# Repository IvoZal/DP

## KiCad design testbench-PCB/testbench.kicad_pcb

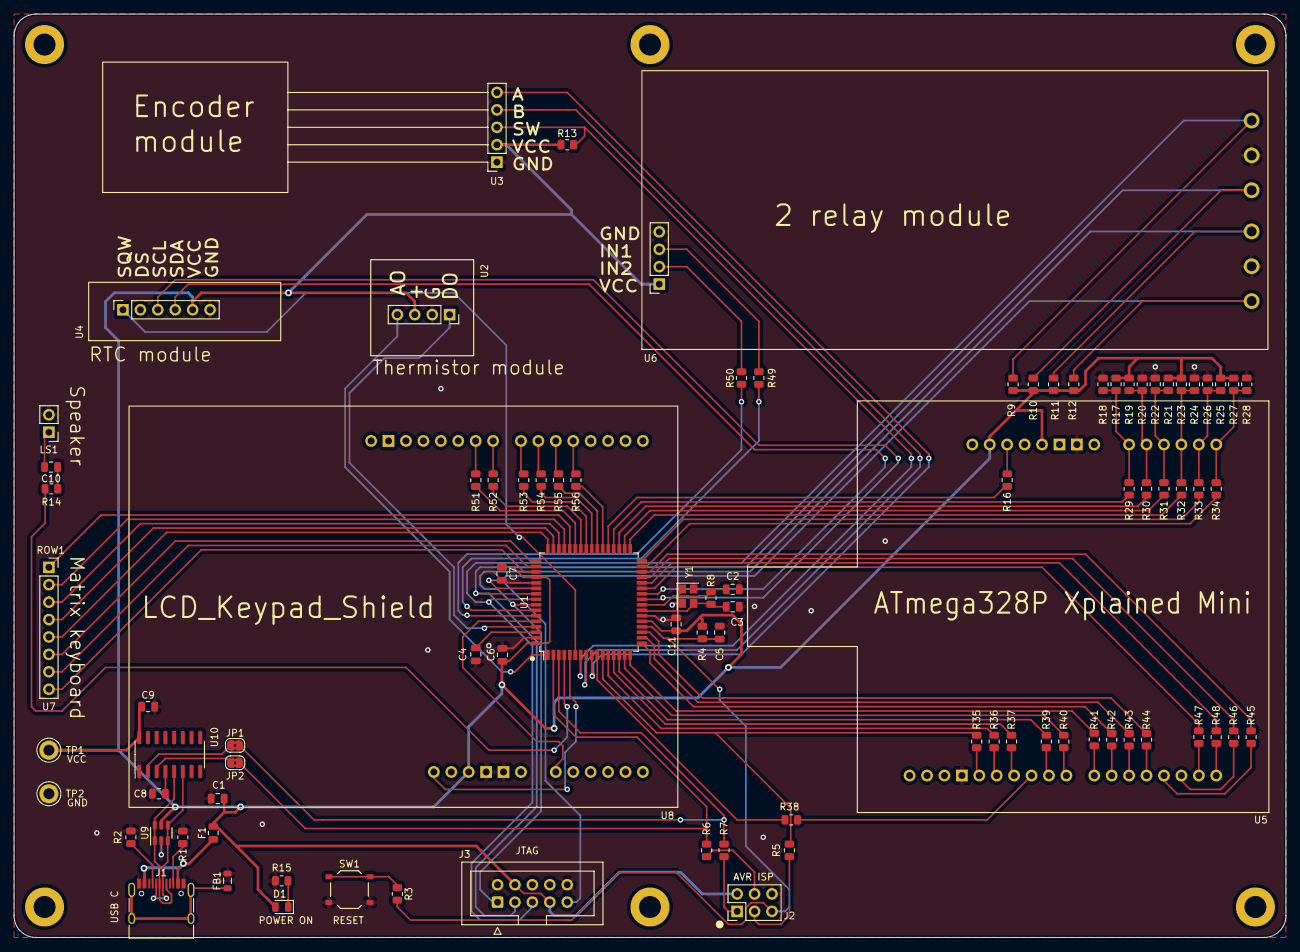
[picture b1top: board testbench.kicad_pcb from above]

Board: 2 copper layers, 185.4 x 134.6 mm, 90 parts (0 on the bottom side), 105 nets.

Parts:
C1: 4.7uF; C_0805_2012Metric
C2, C3: 22p; C_0805_2012Metric
C4, C5, C6, C7, C8, C9, C11: 100n; C_0805_2012Metric
C10: 1uF; C_0805_2012Metric
D1: LED; LED_0805_2012Metric
F1: 500mA; Fuse_0805_2012Metric
FB1: 100R@100MHz; L_0805_2012Metric
J1: USB_C_Receptacle_USB2.0; USB_C_Receptacle_HRO_TYPE-C-31-M-12
J2: AVR-ISP; PinHeader_2x03_P2.54mm_Vertical
J3: AVR-JTAG; IDC-Header_2x05_P2.54mm_Vertical
JP1, JP2: SolderJumper_2_Bridged; SolderJumper-2_P1.3mm_Bridged2Bar_RoundedPad1.0x1.5mm
LS1: Speaker; PinHeader_1x02_P2.54mm_Vertical
R1, R2: 5.1k; R_0805_2012Metric
R3, R5, R6, R7, R16, R29, R30, R31, R32, R33, R34, R35, R36, R37, R38, R39, R40, R41, R42, R43, R44, R45, R46, R47, R48, R49, R50, R51, R52, R53, R54, R55, R56: 330R; R_0805_2012Metric
R4: 4.7k; R_0805_2012Metric
R8: 1M; R_0805_2012Metric
R9, R10, R11, R12, R13: 10k; R_0805_2012Metric
R14: 200R; R_0805_2012Metric
R15: 470R; R_0805_2012Metric
R17, R18, R19, R20, R21, R22, R23, R24, R25, R26, R27, R28: 1k; R_0805_2012Metric
SW1: SW_Push; SW_Push_1P1T_XKB_TS-1187A
TP1, TP2: TestPoint; TestPoint_Keystone_5005-5009_Compact
U1: ATmega2561-16A; TQFP-64_14x14mm_P0.8mm
U2: Thermistor_module
U3: Rotary_encoder_switch_module; Rotary_encoder_module
U4: RTC_EEPROM_module; RTC_module
U5: ATmega328P_Xplained_mini
U6: Relay_module
U7: Matrix_keyboard; PinSocket_1x08_P2.54mm_Vertical
U8: LCD_display; LCD_1602A_module
U9: USBLC6-2SC6; SOT-23-6
U10: CH340C; SOIC-16_3.9x9.9mm_P1.27mm
Y1: X322516MLB4SI; Oscillator_SMD_Abracon_ASE-4Pin_3.2x2.5mm

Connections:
+5V: C1.1, C6.1, C7.1, C9.1, C11.1, D1.2 (A), F1.2, J2.2 (VCC), J3.4 (VREF), J3.7 (VCC), R4.1, R9.1, R10.1, R11.1, R12.1, R13.1, R17.1, R19.1, R21.1, R23.1, R25.1, R27.1, TP1.1, U1.21 (VCC), U1.52 (VCC), U1.64 (AVCC), U2.3 (+), U3.4 (+), U4.5 (VCC), U5.20 (VCC), U5.23 (5V), U6.4 (Vcc), U8.19 (5V), U9.5 (VBUS), U10.16 (VCC)
/ATmega328P module/D0: R16.2, U5.21 (~RESET/PC6)
/ATmega328P module/D1: R17.2, R18.1, R29.2, U5.27 (PC0)
/ATmega328P module/D2: R19.2, R20.1, R30.2, U5.28 (PC1)
/ATmega328P module/D3: R21.2, R22.1, R31.2, U5.29 (PC2)
/ATmega328P module/D4: R23.2, R24.1, R32.2, U5.30 (PC3)
/ATmega328P module/D5: R25.2, R26.1, R33.2, U5.31 (PC4)
/ATmega328P module/D6: R27.2, R28.1, R34.2, U5.32 (PC5)
/ATmega328P module/D7: R35.1, U5.14 (PB5)
/ATmega328P module/D8: R36.1, U5.13 (PB4)
/ATmega328P module/D9: R37.1, U5.12 (PB3)
/ATmega328P module/D10: R38.1, U5.11 (PB2)
/ATmega328P module/D11: R39.1, U5.10 (PB1)
/ATmega328P module/D12: R40.1, U5.9 (PB0)
/ATmega328P module/D13: R41.1, U5.8 (PD7)
/ATmega328P module/D14: R42.1, U5.7 (PD6)
/ATmega328P module/D15: R43.1, U5.6 (PD5)
/ATmega328P module/D16: R44.1, U5.5 (PD4)
/ATmega328P module/D17: R45.1, U5.4 (PD3)
/ATmega328P module/D18: R46.1, U5.3 (PD2)
/ATmega328P module/D19: R47.1, U5.2 (PD1)
/ATmega328P module/D20: R48.1, U5.1 (PD0)
/ATmega328P module/DUT_D0: R16.1, U1.37 (PC2)
/ATmega328P module/DUT_D1: R29.1, U1.36 (PC1)
/ATmega328P module/DUT_D2: R30.1, U1.35 (PC0)
/ATmega328P module/DUT_D3: R31.1, U1.34 (PG1)
/ATmega328P module/DUT_D4: R32.1, U1.33 (PG0)
/ATmega328P module/DUT_D5: R33.1, U1.32 (PD7)
/ATmega328P module/DUT_D6: R34.1, U1.31 (PD6)
/ATmega328P module/DUT_D7: R48.2, U1.28 (PD3)
/ATmega328P module/DUT_D8: R47.2, U1.27 (PD2)
/ATmega328P module/DUT_D9: R46.2, U1.29 (PD4)
/ATmega328P module/DUT_D10: R45.2, U1.30 (PD5)
/ATmega328P module/DUT_D11: R44.2, U1.19 (PG4)
/ATmega328P module/DUT_D12: R43.2, U1.18 (PG3)
/ATmega328P module/DUT_D13: R42.2, U1.17 (PB7)
/ATmega328P module/DUT_D14: R41.2, U1.16 (PB6)
/ATmega328P module/DUT_D15: R40.2, U1.15 (PB5)
/ATmega328P module/DUT_D16: R39.2, U1.14 (PB4)
/ATmega328P module/DUT_D17: R38.2, U1.10 (PB0)
/ATmega328P module/DUT_D18: R37.2, U1.13 (PB3)
/ATmega328P module/DUT_D19: R36.2, U1.12 (PB2)
/ATmega328P module/DUT_D20: R5.1, R35.2, U1.11 (PB1)
/Kit modules/ENC.A: U1.9 (PE7), U3.1 (CLK)
/Kit modules/ENC.B: U1.8 (PE6), U3.2 (DT)
/Kit modules/ENC.SW: R13.2, U1.7 (PE5), U3.3 (SW)
/Kit modules/I2C_SCL: U1.25 (PD0), U4.3 (SCL)
/Kit modules/I2C_SDA: U1.26 (PD1), U4.4 (SDA)
/Kit modules/K1-IN: R49.1, U1.58 (PF3)
/Kit modules/K1-NC: J3.5 (TMS), R9.2, U1.56 (PF5), U6.5 (K1-NC)
/Kit modules/K1-NO: J3.3 (TDO), R10.2, U1.55 (PF6), U6.7 (K1-NO)
/Kit modules/K2-IN: R50.1, U1.59 (PF2)
/Kit modules/K2-NC: J3.1 (TCK), R11.2, U1.57 (PF4), U6.8 (K2-NC)
/Kit modules/K2-NO: J3.9 (TDI), R12.2, U1.54 (PF7), U6.10 (K2-NO)
/Kit modules/KEY_D0: U1.44 (PA7), U7.1 (ROW1)
/Kit modules/KEY_D1: U1.45 (PA6), U7.2 (ROW2)
/Kit modules/KEY_D2: U1.46 (PA5), U7.3 (ROW3)
/Kit modules/KEY_D3: U1.47 (PA4), U7.4 (ROW4)
/Kit modules/KEY_D4: U1.48 (PA3), U7.5 (COL1)
/Kit modules/KEY_D5: U1.49 (PA2), U7.6 (COL2)
/Kit modules/KEY_D6: U1.50 (PA1), U7.7 (COL3)
/Kit modules/KEY_D7: U1.51 (PA0), U7.8 (COL4)
/Kit modules/LCD_AO: U1.60 (PF1), U8.23 (A0)
/Kit modules/LCD_D0: R56.2, U1.38 (PC3)
/Kit modules/LCD_D1: R55.2, U1.39 (PC4)
/Kit modules/LCD_D2: R54.2, U1.40 (PC5)
/Kit modules/LCD_D3: R53.2, U1.41 (PC6)
/Kit modules/LCD_D4: R52.2, U1.42 (PC7)
/Kit modules/LCD_D5: R51.2, U1.43 (PG2)
/Kit modules/LCD_D6: U1.5 (PE3), U8.17 (RST)
/Kit modules/RTC_SQW: U1.6 (PE4), U4.1 (SQ)
/Kit modules/Speaker_IN: R14.1, U1.4 (PE2)
/Kit modules/Thermistor_AO: U1.61 (PF0), U2.1 (AO)
/Kit modules/Thermistor_DO: U1.1 (PG5), U2.4 (DO)
/MCU/RST: C5.1, J2.5 (~RST), R3.2, R4.2, U1.20 (~RESET)
/MCU/UART0_RXD: JP2.2 (B), R6.1, U1.2 (PE0)
/MCU/UART0_TXD: JP1.2 (B), R7.1, U1.3 (PE1)
/USB Interface/VBUS: F1.1, J1.A4 (VBUS), J1.A9 (VBUS), J1.B4 (VBUS), J1.B9 (VBUS)
GND: C1.2, C2.1, C3.1, C4.2, C5.2, C6.2, C7.2, C8.2, C9.2, C11.2, FB1.2, J1.A1 (GND), J1.A12 (GND), J1.B1 (GND), J1.B12 (GND), J2.6 (GND), J3.2 (GND), J3.10 (GND), LS1.2, R1.2, R2.2, R15.2, R18.2, R20.2, R22.2, R24.2, R26.2, R28.2, SW1.2, TP2.1, U1.22 (GND), U1.53 (GND), U1.63 (GND), U2.2 (GND), U3.5 (GND), U4.6 (GND), U5.15 (GND), U5.25 (GND), U6.1 (GND), U6.6 (K1-COM), U6.9 (K2-COM), U8.20 (GND), U8.21 (GND), U9.2 (GND), U10.1 (GND), Y1.2, Y1.4
unnamed: C10.1, R14.2
unnamed: C10.2, LS1.1
unnamed: D1.1 (K), R15.1
unnamed: J1.A5 (CC1), R2.1
unnamed: J1.B5 (CC2), R1.1
unnamed: FB1.1, J1.S1 (SHIELD)
unnamed: J2.1 (MISO), R7.2
unnamed: J2.4 (MOSI), R6.2
unnamed: J2.3 (SCK), R5.2
unnamed: JP1.1 (A), U10.2 (TXD)
unnamed: JP2.1 (A), U10.3 (RXD)
unnamed: R3.1, SW1.1
unnamed: C4.1, U1.62 (AREF)
unnamed: C2.2, R8.1, U1.24 (XTAL1), Y1.1
unnamed: C3.2, R8.2, U1.23 (XTAL2), Y1.3
unnamed: R49.2, U6.2 (IN1)
unnamed: R50.2, U6.3 (IN2)
unnamed: R56.1, U8.5 (D4)
unnamed: R55.1, U8.6 (D5)
unnamed: R54.1, U8.7 (D6)
unnamed: R53.1, U8.8 (D7)
unnamed: R51.1, U8.10 (E)
unnamed: R52.1, U8.9 (RS)
unnamed: J1.A6 (D+), J1.B6 (D+), U9.1 (I/O1), U9.6 (I/O1), U10.5 (UD+)
unnamed: J1.A7 (D-), J1.B7 (D-), U9.3 (I/O2), U9.4 (I/O2), U10.6 (UD-)
unnamed: C8.1, U10.4 (V3)

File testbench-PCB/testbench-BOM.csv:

"Id";"Designator";"Footprint";"Quantity";"Designation";"Supplier and ref";
1;"U8";"LCD_1602A_module";1;"LCD_display";;;
2;"C4,C7,C9,C11,C8,C6,C5";"C_0805_2012Metric";7;"100n";;;
3;"U6";"Relay_module";1;"Relay_module";;;
4;"C10";"C_0805_2012Metric";1;"1uF";;;
5;"R23,R17,R21,R28,R20,R27,R22,R24,R18,R25,R19,R26";"R_0805_2012Metric";12;"1k";;;
6;"C3,C2";"C_0805_2012Metric";2;"22p";;;
7;"R2,R1";"R_0805_2012Metric";2;"5.1k";;;
8;"R10,R12,R11,R13,R9";"R_0805_2012Metric";5;"10k";;;
9;"R7,R5,R6,R3";"R_0805_2012Metric";4;"330R";;;
10;"D1";"LED_0805_2012Metric";1;"LED";;;
11;"J1";"USB_C_Receptacle_HRO_TYPE-C-31-M-12";1;"USB_C_Receptacle_USB2.0";;;
12;"U9";"SOT-23-6";1;"USBLC6-2SC6";;;
13;"U1";"TQFP-64_14x14mm_P0.8mm";1;"ATmega2561-16A";;;
14;"J2";"PinHeader_2x03_P2.54mm_Vertical";1;"AVR-ISP";;;
15;"R14";"R_0805_2012Metric";1;"200R";;;
16;"TP2 GND,TP1 +5V";"TestPoint_Keystone_5005-5009_Compact";2;"TestPoint";;;
17;"R8";"R_0805_2012Metric";1;"1M";;;
18;"U4";"RTC_module";1;"RTC_EEPROM_module";;;
19;"U7";"PinSocket_1x08_P2.54mm_Vertical";1;"Matrix_keyboard";;;
20;"C1";"C_0805_2012Metric";1;"10u";;;
21;"U2";"Thermistor_module";1;"Thermistor_module";;;
22;"U10";"SOIC-16_3.9x9.9mm_P1.27mm";1;"CH340C";;;
23;"JP2,JP1";"SolderJumper-2_P1.3mm_Bridged2Bar_RoundedPad1.0x1.5mm";2;"SolderJumper_2_Bridged";;;
24;"FB1";"L_0805_2012Metric";1;"100R@100MHz";;;
25;"R4";"R_0805_2012Metric";1;"4.7k";;;
26;"Y1";"Oscillator_SMD_Abracon_ASE-4Pin_3.2x2.5mm";1;"X322516MLB4SI";;;
27;"R15";"R_0805_2012Metric";1;"500R";;;
28;"LS1";"PinHeader_1x02_P2.54mm_Vertical";1;"Speaker";;;
29;"J3";"IDC-Header_2x05_P2.54mm_Vertical";1;"AVR-JTAG";;;
30;"U3";"Rotary_encoder_module";1;"Rotary_encoder_switch_module";;;
31;"SW1";"SW_Push_1P1T_XKB_TS-1187A";1;"SW_Push";;;
32;"F1";"Fuse_1812_4532Metric";1;"Polyfuse";;;
33;"U5";"ATmega328P_Xplained_mini";1;"~";;;

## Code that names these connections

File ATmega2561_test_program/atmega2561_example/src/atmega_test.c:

/*
 * atmega_test.c
 *
 * Created: 01.03.2024 11:15:49
 *  Author: Ivo Zaludek
 */ 

#include "module_test.h"

/* Pin define on ATmega2561 side */
//#define D0 (1 << PC2)		// m328p RESET
#define D1 (1 << PC1)
#define D2 (1 << PC0)
#define D3 (1 << PG1)
#define D4 (1 << PG0)
#define D5 (1 << PD7)
#define D6 (1 << PD6)
//#define D7 (1 << PD3)		// m328p USART rx
//#define D8 (1 << PD2)		// m328p USART tx
#define D9 (1 << PD4)
#define D10 (1 << PD5)
#define D11 (1 << PG4)
#define D12 (1 << PG3)
#define D13 (1 << PB7)
#define D14 (1 << PB6)
#define D15 (1 << PB5)
#define D16 (1 << PB4)
#define D17 (1 << PB0)
#define D18 (1 << PB3)
#define D19 (1 << PB2)
#define D20 (1 << PB1)

#define RST PC2				// m328p RESET

#define PB_PINS (D13 | D14 | D15 | D16 | D17 | D18 | D19 | D20)
#define PC_PINS (D1 | D2)
#define PD_PINS (D5 | D6 | D9 | D10)
#define PG_PINS (D3 | D4 | D11 | D12)

/************************************************
Local variables
*************************************************/
bool test_failed = false;

typedef struct pin_connection {
	const uint8_t m2561_port_offset;
	uint8_t m2561_pin;
	const char* m328p_pin_name;	
} PIN_CONNECTION_T;

PIN_CONNECTION_T pin_def[] =
	{{0x06,D1,"PC0"},
	{0x06,D2,"PC1"},
	{0x12,D3,"PC2"},
	{0x12,D4,"PC3"},
	{0x12,D5,"PC4"},
	{0x09,D6,"PC5"},
	//{0x09,D7,"PD0"},
	//{0x09,D8,"PD1"},
	{0x09,D9,"PD2"},
	{0x09,D10,"PD3"},
	{0x12,D11,"PD4"},
	{0x12,D12,"PD5"},
	{0x03,D13,"PD6"},
	{0x03,D14,"PD7"},
	{0x03,D15,"PB0"},
	{0x03,D16,"PB1"},
	{0x03,D17,"PB2"},
	{0x03,D18,"PB3"},
	{0x03,D19,"PB4"},
	{0x03,D20,"PB5"}};
		
/************************************************
Function declaration
*************************************************/
static void dio_input_test(bool tested_value, bool* comm_fail)
{
	char input_string[BUFFER_SIZE];
	
	PORTB_set_port_level(PB_PINS, tested_value);
	PORTC_set_port_level(PC_PINS, tested_value);
	PORTD_set_port_level(PD_PINS, tested_value);
	PORTG_set_port_level(PG_PINS, tested_value);
	
	char tested_char;
	if(tested_value == true)
		tested_char = 0x30;	// "0"
	else
		tested_char = 0x31; // "1"
		
	fprintf(&UART_1_stream,"dio_high_PD3\n");
	
	for(uint8_t i=0; i < sizeof(pin_def)/sizeof(PIN_CONNECTION_T); i++)
	{
		fprintf(&UART_1_stream,"dio_read_%s\n",pin_def[i].m328p_pin_name);
		uint32_t timestamp = getTime() + 50000;	// set response timeout
		while(timestamp > getTime())
		{
			if((UART1_buf_peek_head() == 0xA) && (UART1_buf_length() > 0))	// if the last char was line feed
			{
				for(uint8_t j=0; j < BUFFER_SIZE; j++)
				{
					if(UART1_buf_length() > 0)
						input_string[j] = UART1_buf_get();
					else
						input_string[j] = 0;
				}
				if(input_string[4] == tested_char)
				{
					printf("FAIL: %s\n",pin_def[i].m328p_pin_name);
					test_failed = true;
				}
				else if(input_string[4] == 0)
					*comm_fail = true;
				timestamp = 0;
			}
		}
		if(timestamp > 0)
			*comm_fail = true;
	}
}

static void dio_output_test(void)
{
	for(uint8_t i=0; i < sizeof(pin_def)/sizeof(PIN_CONNECTION_T); i++)
	{
		fprintf(&UART_1_stream,"dio_high_%s\n",pin_def[i].m328p_pin_name);
	}
	delay(50000);
	if((PORTB_get_port_level(0) & PB_PINS) != PB_PINS) {
		printf("FAIL: PORTB ");
		test_failed = true;
	}
	if((PORTC_get_port_level(0) & PC_PINS) != PC_PINS) {
		printf("FAIL: PORTC ");
		test_failed = true;
	}
	if((PORTD_get_port_level(0) & PD_PINS) != PD_PINS) {
		printf("FAIL: PORTD ");
		test_failed = true;
	}
	if((PORTG_get_port_level(0) & PG_PINS) != PG_PINS) {
		printf("FAIL: PORTG ");
		test_failed = true;
	}
		
	for(uint8_t i=0; i < sizeof(pin_def)/sizeof(PIN_CONNECTION_T); i++)
	{
		fprintf(&UART_1_stream,"dio_low_%s\n",pin_def[i].m328p_pin_name);
	}
	delay(50000);
	if((PORTB_get_port_level(0) & PB_PINS) != 0) {
		printf("FAIL: PORTB ");
		test_failed = true;
	}
	if((PORTC_get_port_level(0) & PC_PINS) != 0) {
		printf("FAIL: PORTC ");
		test_failed = true;
	}
	if((PORTD_get_port_level(0) & PD_PINS) != 0) {
		printf("FAIL: PORTD ");
		test_failed = true;
	}
	if((PORTG_get_port_level(0) & PG_PINS) != 0) {
		printf("FAIL: PORTG ");
		test_failed = true;
	}
}

static uint16_t adc_receive(bool* comm_fail)
{
	uint32_t timestamp = getTime() + 50000;	// set response timeout
	while(timestamp > getTime())
	{
		if((UART1_buf_peek_head() == 0xA) && (UART1_buf_length() > 0))	// if the last char was line feed
		{
			uint16_t adc_val = 0;
			char buf_ch = 0;
			while((buf_ch != 0x3D) && (UART1_buf_length() > 0))
			{
				buf_ch = UART1_buf_get();
			}
			while((buf_ch != 0xA) && (UART1_buf_length() > 0))
			{
				uint8_t buf_ch = UART1_buf_get();
				if(buf_ch > 0x29 && buf_ch < 0x3A)
				{
					adc_val = adc_val * 10U;
					adc_val += buf_ch - 0x30;
				}
				else if(buf_ch != 0xA)
					*comm_fail = true;
			}
			timestamp = 0;
			return adc_val;
		}
	}
	if(timestamp > 0)
		*comm_fail = true;
	return 0xFFFF;
}

static void adc_test(bool* comm_fail)
{	
	/* Set atmega2561 pins to Hi-Z */
	PORTB_set_port_dir(PB_PINS, PORT_DIR_IN);
	PORTC_set_port_dir(PC_PINS, PORT_DIR_IN);
	PORTD_set_port_dir(PD_PINS, PORT_DIR_IN);
	PORTG_set_port_dir(PG_PINS, PORT_DIR_IN);
	
	uint16_t adc_val;
	fprintf(&UART_1_stream,"aio_read_ADCF\n");
	adc_val = adc_receive(comm_fail);
	if(adc_val > 20) {
		printf("FAIL: ADC 0V REF");
		test_failed = true;
	}
	
	fprintf(&UART_1_stream,"aio_read_ADCE\n");
	adc_receive(comm_fail);
	delay(1000);	// wait for the reference voltage to stabilize
	// read stabilized voltage reference
	fprintf(&UART_1_stream,"aio_read_ADCE\n");
	adc_val = adc_receive(comm_fail);
	if(adc_val < 160 || adc_val > 270)
	{
		printf("FAIL: ADC VBG REF: %u",adc_val);
		test_failed = true;
	}
	
	/* For ADC channel 0 to 5 */
	for(uint8_t adc_ch=0; adc_ch <= 0x5; adc_ch++)
	{
		fprintf(&UART_1_stream,"aio_read_ADC%u\n",adc_ch);
		adc_val = adc_receive(comm_fail);
		if(adc_val < 410 || adc_val > 613)
		{
			printf("FAIL: ADC%u",adc_ch);
			test_failed = true;
		}
	}
	
	/* Set atmega2561 pins as output */
	PORTB_set_port_dir(PB_PINS, PORT_DIR_OUT);
	PORTC_set_port_dir(PC_PINS, PORT_DIR_OUT);
	PORTD_set_port_dir(PD_PINS, PORT_DIR_OUT);
	PORTG_set_port_dir(PG_PINS, PORT_DIR_OUT);
	
	PORTB_set_port_level(PB_PINS, false);
	PORTC_set_port_level(PC_PINS, false);
	PORTD_set_port_level(PD_PINS, false);
	PORTG_set_port_level(PG_PINS, false);
	
	/* For ADC channel 0 to 5 */
	for(uint8_t adc_ch=0; adc_ch <= 0x5; adc_ch++)
	{
		fprintf(&UART_1_stream,"aio_read_ADC%u\n",adc_ch);
		adc_val = adc_receive(comm_fail);
		if(adc_val < 170 || adc_val > 255)
		{
			printf("FAIL: ADC%u",adc_ch);
			test_failed = true;
		}
	}
	
	PORTB_set_port_level(PB_PINS, true);
	PORTC_set_port_level(PC_PINS, true);
	PORTD_set_port_level(PD_PINS, true);
	PORTG_set_port_level(PG_PINS, true);
	
	/* For ADC channel 0 to 5 */
	for(uint8_t adc_ch=0; adc_ch <= 0x5; adc_ch++)
	{
		fprintf(&UART_1_stream,"aio_read_ADC%u\n",adc_ch);
		adc_val = adc_receive(comm_fail);
		if(adc_val < 607 || adc_val > 911)
		{
			printf("FAIL: ADC%u",adc_ch);
			test_failed = true;
		}
	}
}

void atmega_test(void)
{
	/* Set atmega2561 pins as output */
	PORTB_set_port_dir(PB_PINS, PORT_DIR_OUT);
	PORTC_set_port_dir(PC_PINS, PORT_DIR_OUT);
	PORTD_set_port_dir(PD_PINS, PORT_DIR_OUT);
	PORTG_set_port_dir(PG_PINS, PORT_DIR_OUT);
	
	bool comm_fail = false;
	test_failed = false;
	
	/* Read both logical values */
	dio_input_test(true, &comm_fail);
	if(!comm_fail)
	{
		dio_input_test(false, &comm_fail);
	}
	
	/* Set atmega2561 pins as input */
	PORTB_set_port_dir(PB_PINS, PORT_DIR_IN);
	PORTC_set_port_dir(PC_PINS, PORT_DIR_IN);
	PORTD_set_port_dir(PD_PINS, PORT_DIR_IN);
	PORTG_set_port_dir(PG_PINS, PORT_DIR_IN);
	
	/* Set both logical values */
	if(!comm_fail)
	{
		dio_output_test();
		adc_test(&comm_fail);
	}
	
	if(comm_fail)
	{
		printf("FAIL: COMMUNICATION\n");
		test_failed = true;
	}
	if(test_failed == false)
	{
		printf("PASS");
	}
	printf("\n");
}

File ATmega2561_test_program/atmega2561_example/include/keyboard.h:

/*
 * keyboard.h - library for matrix keyboard
 *
 * Created: 16.03.2023 20:31:06
 *  Author: Ivo Zaludek
 *
 * This header file contains function and variable declarations for
 * the lcd.h library. These declarations are needed by any code
 * that uses the library, so this file should be included in all source
 * files that use the library.
 *
 * Note: This file should be included after any system or third-party
 * header files that are needed by the library. 
 */ 


#ifndef KEYBOARD_H_
#define KEYBOARD_H_

#include <avr/io.h>

/* Pinout definitions */
#define Row1 (1 << PA0)
#define Row2 (1 << PA1)
#define Row3 (1 << PA2)
#define Row4 (1 << PA3)
#define Col1 (1 << PA4)
#define Col2 (1 << PA5)
#define Col3 (1 << PA6)
#define Col4 (1 << PA7)

#define ALL_ROWS (Row1 | Row2 | Row3 | Row4)
#define ALL_COL (Col1 | Col2 | Col3 | Col4)

#define BTN_NUM 16

/* Function returns index of pressed button on the matrix keyboard */
uint8_t KeyboardReadIdx();

/* Function returns pressed button on the matrix keyboard as a char. */
char KeyboardRead();

#endif /* KEYBOARD_H_ */

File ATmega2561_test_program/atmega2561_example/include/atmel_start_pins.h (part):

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#include <port.h>

/**
 * \brief Set PB1 pull mode
 *
 * Configure pin to pull up, down or disable pull mode, supported pull
 * modes are defined by device used
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}

/**
 * \brief Set PB1 data direction
 *
 * Select if the pin data direction is input, output or disabled.
 * If disabled state is not possible, this function throws an assert.
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}

/**
 * \brief Set PB1 level
 *
 * Sets output level on a pin
 *
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}

/**
 * \brief Toggle output level on PB1
 *
 * Toggle the pin level
 */
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}

/**
 * \brief Get level on PB1
 *
 * Reads the level on a pin
 */
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}

/**
 * \brief Set PB2 pull mode
 *
 * Configure pin to pull up, down or disable pull mode, supported pull
 * modes are defined by device used
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}

/**
 * \brief Set PB2 data direction
 *
 * Select if the pin data direction is input, output or disabled.
 * If disabled state is not possible, this function throws an assert.
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}

/**
 * \brief Set PB2 level
 *
 * Sets output level on a pin
 *
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}

/**
 * \brief Toggle output level on PB2
 *
 * Toggle the pin level
 */
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}

/**
 * \brief Get level on PB2
 *
 * Reads the level on a pin
 */
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}

/**
 * \brief Set PB3 pull mode
 *
 * Configure pin to pull up, down or disable pull mode, supported pull
 * modes are defined by device used
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}

/**
 * \brief Set PB3 data direction
 *
 * Select if the pin data direction is input, output or disabled.
 * If disabled state is not possible, this function throws an assert.
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}

/**
 * \brief Set PB3 level
 *
 * Sets output level on a pin
 *
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}

/**
 * \brief Toggle output level on PB3
 *
 * Toggle the pin level
 */
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}

/**
 * \brief Get level on PB3
 *
 * Reads the level on a pin
 */
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}

/**
 * \brief Set PD2 pull mode
 *
 * Configure pin to pull up, down or disable pull mode, supported pull
 * modes are defined by device used
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}

/**
 * \brief Set PD2 data direction
 *
 * Select if the pin data direction is input, output or disabled.
 * If disabled state is not possible, this function throws an assert.
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}

/**
 * \brief Set PD2 level
 *
 * Sets output level on a pin
 *
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}

/**
 * \brief Toggle output level on PD2
 *
 * Toggle the pin level
 */
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}

/**
 * \brief Get level on PD2
 *
 * Reads the level on a pin
 */
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}

/**
 * \brief Set PD3 pull mode
 *
 * Configure pin to pull up, down or disable pull mode, supported pull
 * modes are defined by device used
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}

/**
 * \brief Set PD3 data direction
 *
 * Select if the pin data direction is input, output or disabled.
 * If disabled state is not possible, this function throws an assert.
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}

/**
 * \brief Set PD3 level
 *
 * Sets output level on a pin
 *
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}

/**
 * \brief Toggle output level on PD3
 *
 * Toggle the pin level
 */
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}

/**
 * \brief Get level on PD3
 *
 * Reads the level on a pin
 */
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}

/**
 * \brief Set PE0 pull mode
 *
 * Configure pin to pull up, down or disable pull mode, supported pull
 * modes are defined by device used
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}

/**
 * \brief Set PE0 data direction
 *
 * Select if the pin data direction is input, output or disabled.
 * If disabled state is not possible, this function throws an assert.
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}

/**
 * \brief Set PE0 level
 *
 * Sets output level on a pin
 *
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}

/**
 * \brief Toggle output level on PE0
 *
 * Toggle the pin level
 */
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}

/**
 * \brief Get level on PE0
 *
 * Reads the level on a pin
 */
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}

/**
 * \brief Set PE1 pull mode
 *
 * Configure pin to pull up, down or disable pull mode, supported pull
 * modes are defined by device used
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}

/**
 * \brief Set PE1 data direction
 *
 * Select if the pin data direction is input, output or disabled.
 * If disabled state is not possible, this function throws an assert.
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}

/**
 * \brief Set PE1 level
 *
 * Sets output level on a pin
 *
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}

/**
 * \brief Toggle output level on PE1
 *
 * Toggle the pin level
 */
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}

/**
 * \brief Get level on PE1
 *
 * Reads the level on a pin
 */
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
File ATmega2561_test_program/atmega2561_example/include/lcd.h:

/*
 * lcd.h - library for 4 bit communication with HD44780U lcd display
 *
 * Created: 09.03.2023 21:32:36
 *  Author: Ivo Zaludek
 *
 * This header file contains function and variable declarations for
 * the lcd.h library. These declarations are needed by any code
 * that uses the library, so this file should be included in all source
 * files that use the library.
 *
 * Note: This file should be included after any system or third-party
 * header files that are needed by the library.
 */

#ifndef LCD_H_
#define LCD_H_

#include <avr/io.h>
#include <stdbool.h>
#include <stdio.h>
#include <stdlib.h>
#include "timer.h"

#define DB4 (1 << PC3)
#define DB5 (1 << PC4)
#define DB6 (1 << PC5)
#define DB7 (1 << PC6)
#define RS (1 << PC7)
#define E (1 << PG2)
#define DB_MASK (DB4 | DB5 | DB6 | DB7)

/* Display initialization, call after power on. */
void lcd_Init();

/* Send only lower 4 bits of cmd command. Used for initialization. */
void lcd_SendCmd4b(uint8_t cmd);

/* Function sends 8 bit command cmd to display. */
void lcd_SendCmd(uint8_t cmd);

/* Function sends 8 bit character data to display. */
void lcd_WriteChar(char data);

/* Sets DDRAM address 0 in address counter. 
Also returns display from being shifted to original position */
void lcd_RetHome();

/* Sets DDRAM address. */
void lcd_SetCursor(uint8_t address);

/* Shifts display or cursor left or right. 
Negative "shift" shifts display abs(shift) times left, positive shifts right.
Set sc to true to shift display, false to shift cursor. */
void lcd_Shift(int8_t shift, bool sc);

/* Clear the display and returns to home position. */
void lcd_Clear();

/* Putchar function for stream print. */
int lcd_putchar(char c, FILE *stream);

/* Definition of stream display. */
extern FILE display;

#endif /* LCD_H_ */

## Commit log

2023-10-02 project initialization, added README
2023-10-29 Added gitignore.
2023-10-29 Added project, schematics.
2023-10-29 Updated gitignore.
2023-10-29 Fixed gitignore.
2023-10-30 Added the rest of kit modules.
2023-10-30 Added minimal MCU circuit, power supply from USB.
2023-10-30 Changed USB interface name, MCU moved to separate sheet.
2023-10-30 Renamed whole project.
2023-11-05 Added USB interface.
2023-11-06 Added connection between some modules.
2023-11-07 Finished connection between modules and MCU.
2023-11-08 Added footprints to few parts.
2023-11-09 Changed naming convention.
2023-11-11 Connecter speaker, added JTAG.
2023-11-11 Created PCB, changed footprints for symbols.
2023-11-12 Updated footprints, PCB.
2023-11-12 Added submodule with KiCad lib.
2023-11-12 Routed osc., USB interface.
2023-11-14 Rearanged PCB, updated footprints.
2023-11-14 Renamed atmega328p sheet.
2023-11-14 Fixed footprints in schematics.
2023-11-20 Routing the PCB.
2023-11-21 Finished PCB routing, added ground plane.
2023-11-21 Resolved DRC warnings and errors.
2023-11-21 Changes regarding part selection.
2023-11-21 Changed encoder module pinout, added labels.
2023-11-27 Added protective resistors.
2023-11-27 Added logo and label. Rearanged labels.
2023-11-27 DRC resolved.
2023-11-28 Labels moved in schematics.
2023-12-05 Edited relay module output pins.
2023-12-05 Exported fabrication outputs.
2023-12-05 BOM for THT parts.
2023-12-05 Created projects for both MCUs. Added gitignores.
2023-12-05 Copied few libraries from previous poject.
2023-12-05 Deleted duplicate files.
2023-12-13 Added dio lib, edited project
2023-12-30 Added function declaration for dio.
2024-01-04 Added string processing functions.
2024-01-04 Added function which returns the last buffer value.
2024-01-04 Added comparison of input string with strings from cmd_lut.
2024-01-04 Function dio_read fixed.
2024-01-04 String lib function used instead of created one.
2024-01-04 Fixed adc reading.
2024-01-04 Added missing function definition.
2024-01-04 Added type cast - removes warnings.
2024-01-05 Added function description.
2024-01-05 Error returned if invalid cmd passed.
2024-01-05 Deleted unsused files.
2024-01-05 Resolved warnings.
2024-01-05 Added uart lib.
2024-01-05 Deleted unused function.
2024-01-13 Added libraries into main.
2024-01-14 Draft for initial window created.
2024-01-14 Deleted unused files.
2024-01-14 Added start and exit button.
2024-01-16 Added TestModel class for serial communication.
2024-01-16 Moduls sorted by the type of test.
2024-01-19 Updated test_device data structure.
2024-01-19 Fixed message encoding.
2024-01-19 Added TestModel.
2024-01-19 Added test result into default view.
2024-01-24 Added menu for available COM port selection.
2024-01-30 Added exception handling for serial.
2024-01-30 Fixed COM port menu, added label for communication.
2024-01-30 Added method for closing serial.
2024-01-30 Added top level window and a view for reproductor test.
2024-01-31 Added draft for display and thermistor test view.
2024-02-01 Added thermistor test graph, TBD: graph update from serial.
2024-02-01 Added view for graph.
2024-02-02 Thermisor test fixed.
2024-02-02 Fixed UserWarning.
2024-02-02 Added class for user interact, hw evaluate tests.
2024-02-03 Added encoder test case.
2024-02-03 Edited error label printing.
2024-02-03 Added matrix keyboard test case.
2024-02-03 Run all tests in default, concendate error messages.
2024-02-05 Fixed thread while loop condition.
2024-02-05 Added frames around group of features, added error message print.
2024-02-05 Fixed tkinter labels.
2024-02-06 Added GME part names for THT BOM.
2024-02-06 Added Atmel START configured project for ATmega2561.
2024-02-06 Added library for higher level UART handling.
2024-02-06 Added basic main structure.
2024-02-08 Added serial commands, added calling in loop for repeating tests.
2024-02-08 Added function prototypes with functionality description.
2024-02-08 Deleted tc16 library.
2024-02-08 Added reproductor test case.
2024-02-08 Added function for common init, added thermistor test case.
2024-02-08 Added missing test for display buttons.
2024-02-08 Renamed method for serial write.
2024-02-08 Added test case for display button.
2024-02-12 Added missing header include and missing test case.
2024-02-13 Updated the usart-basic lib.
2024-02-13 Added functions to usart_basic lib.
2024-02-13 Reproductor TC working.
2024-02-13 Fixed module_test lib
2024-02-13 Added gitignore for python cache files.
2024-02-16 Added new libraries.
2024-02-17 Changed I2C lib name.
2024-02-17 Changed delay lib for util/delay.h
2024-02-17 Removed warnings.
2024-02-17 Added working encoder library.
2024-02-18 Restored the timer.h library for delay.
2024-02-18 Added full encoder test
2024-02-18 Added stop test function into main.
2024-02-18 Fixed encoder test
2024-02-18 Improved stability of serial, edited error message print.
2024-02-19 Added relay test.
2024-02-22 Error message cleared at start of the test.
2024-02-22 Changed the keyboard library for current schematic.
2024-02-22 Added matrix keyboard test, edited encoder test - fail print timing.
2024-02-22 Added LCD buttons test.
2024-02-23 Added function for register read/write.
2024-02-23 Added RTC test.
2024-02-26 Edited RTC library.
2024-02-26 Fixed relay test, added RTC SQW output test.
2024-02-29 LCD library edited for current schematic.
2024-02-29 Fixed LCD button test.
2024-03-01 LCD library fixed for current schematic.
2024-03-01 Added LCD test.
2024-03-01 Deleted unused i2c library.
2024-03-01 Fixed IIC library - enable in PRR0.
2024-03-01 Fixed strange behavior of RTC test after POR.
2024-03-01 Added file for m328p test, added definition of pins.
2024-03-02 Fixed LCD stream warning.
2024-03-02 USART1 enabled, working.
2024-03-03 Deleted Atmel usart library.
2024-03-03 Use custom UART libarary.
2024-03-03 Deleted usart library from cproj file.
2024-03-03 m328p DIO output test moved into separate function.
2024-03-03 Removed setting reset pin of m328p, fixed pin names.
2024-03-03 Increased delay between messages. SPI init disabled.
2024-03-04 Use custom SPI library.
2024-03-04 Added atmega programming enable.
2024-03-12 Fixed interact_test function, model write fix in progress.
2024-03-13 Added function for SPI block transfer, DUT fuse check.
2024-03-13 Speaker test changed to ISR.
2024-03-13 Added ACK/ERR after reading the message.
2024-03-13 Edited BOM of THT parts.
2024-03-15 Fixed LCD test - delay deleted.
2024-03-15 Added dio output test.
2024-03-16 Added m328p ADC test.
2024-03-16 Fix ADC read function.
2024-03-17 Added PASS print if all tests passed.
2024-03-17 Fixed ADC select, ch E and F.
2024-03-17 Added ADC reference test.
2024-03-17 Fixed LCD and thermistor test.
2024-03-17 Added I2C fail detection. Fixed infinite loop.
2024-03-17 ATmega2561 init functions moved into separate function test_init
2024-03-17 Added test_init call.
2024-03-17 Added "TEST INIT" call, edited empty COM select.
2024-03-17 Added option to (di)select all tests.
2024-03-17 Removed acknowledge print
2024-03-17 Icon created.
2024-03-17 Gitignore edited.
2024-03-18 Added delay for adc reference voltage to stabilize.
2024-03-28 Added avrdude and binary for m328p programming.
2024-03-28 Added GUI for m328p program flashing.
2024-03-28 Added image to LCD module TC.
2024-03-28 Removed m328p flash.
2024-03-30 Fixed stuck communication after programming.
2024-03-30 Added I2C read timeout into EEPROM_read function.
2024-03-30 Added EEPROM test.
2024-03-31 RTC and EEPROM tests split.
2024-03-31 Added menu for test report logging.
2024-04-02 Added photo of LCD module test image.
2024-04-02 File created after submitting its name.
2024-04-02 Added header and report export.
2024-04-04 Fixed eeprom test.
2024-04-04 Edited eeprom test - only first page tested.
2024-04-05 Edited log file GUI
2024-04-05 Testbench number added to csv report log.
2024-04-05 Keyboard test fixed.
2024-04-05 Renamed speaker test command.
2024-04-05 Renamed speaker test.
2024-04-05 Edited report log header write.
2024-04-09 Shorten the delay before fails are printed; minor fix.
2024-04-09 Optimalizations -O1 enabled to delete delay.h warning.
2024-04-09 Edited log file test results export.
2024-04-09 Added executable application.
2024-04-09 Update executable - all files included in single exe file.
2024-04-09 Added bat file for test app export via pyinstaller.
2024-04-09 Added file paths for executable file.
2024-04-15 Removed unused project.
2024-04-29 Added example test report.
2024-04-29 Fixed typo in app gui.
2024-04-29 Added titles to schematics.
